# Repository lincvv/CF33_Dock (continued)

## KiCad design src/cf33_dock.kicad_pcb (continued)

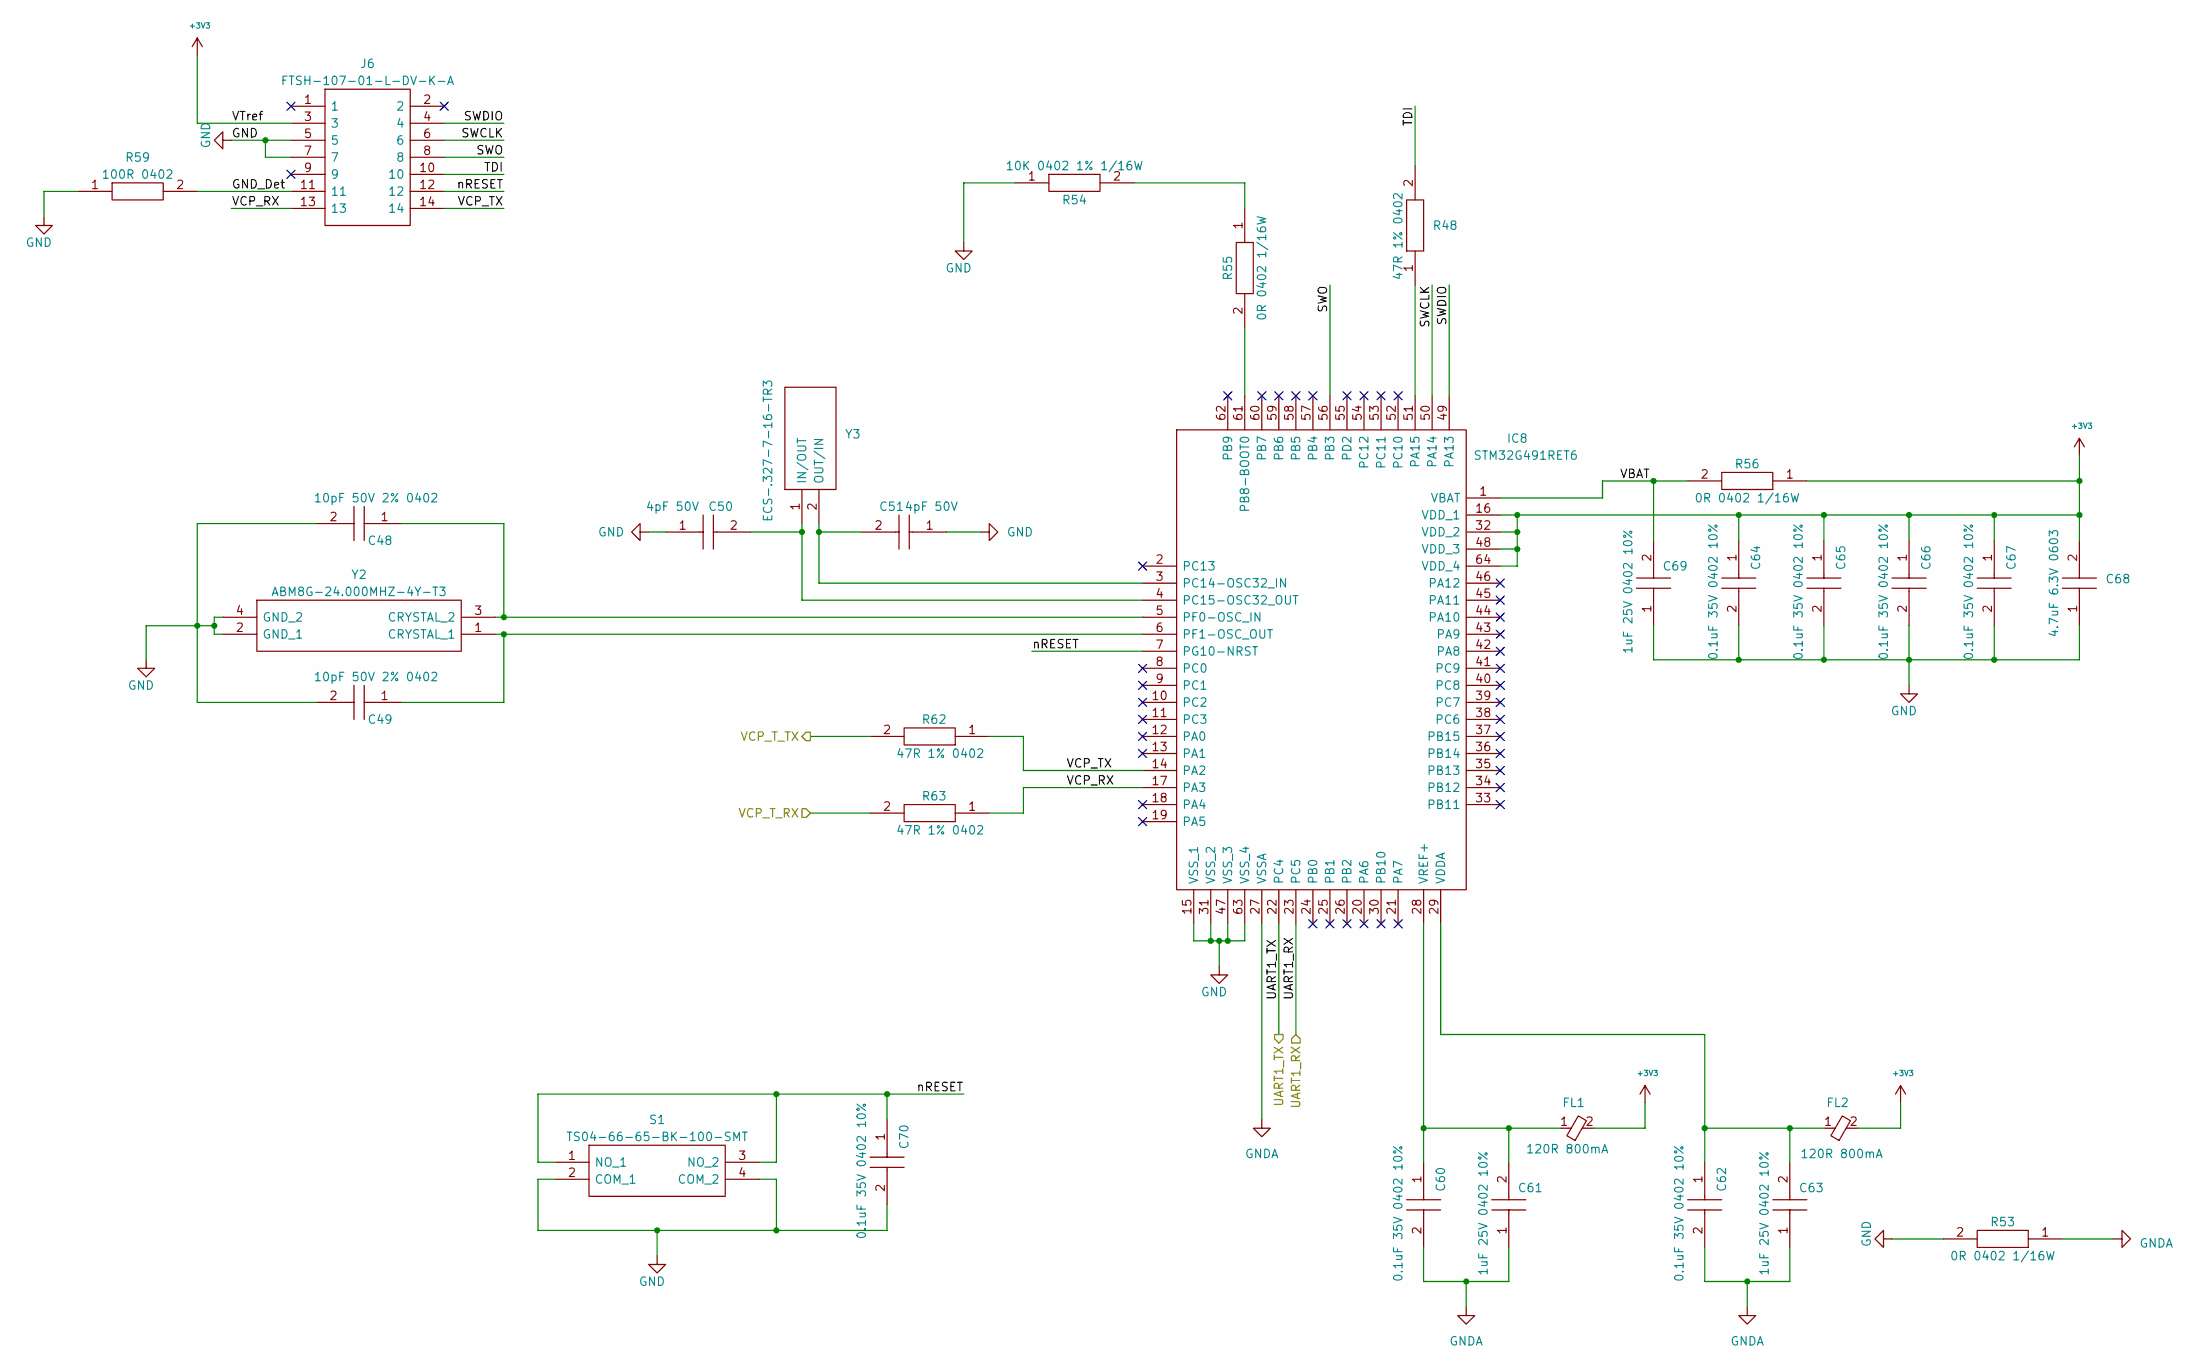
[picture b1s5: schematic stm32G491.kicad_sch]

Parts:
C48, C49: 10pF 50V 2% 0402; C_0402_1005Metric; Manufacturer_Part_Number GJM1555C1H100GB01D; Mouser Part Number 81-GJM1555C1H100GB01
C50, C51: 4pF 50V; R_0402_1005Metric; Manufacturer_Part_Number CQ0402CRNPO9BN4R0
C60, C62, C64, C65, C66, C67, C70: 0.1uF 35V 0402 10%; C_0402_1005Metric; Manufacturer_Part_Number CGA2B3X7R1V104K050BB; Mouser Part Number 810-CGA2B3X7R1V104K
C61, C63, C69: 1uF 25V 0402 10%; C_0402_1005Metric; Manufacturer_Part_Number GRM155R61E105KA12D; Mouser Part Number 81-GRM155R61E105KA2D
C68: 4.7uF 6.3V 0603; CAPC1608X90N; Manufacturer_Part_Number JMK107BB7475KA-T; Mouser Part Number 963-JMK107BB7475KA-T
FL1, FL2: 120R 800mA; BLM18AG102BH1D; Manufacturer_Part_Number BLM18AG121SN1D; Mouser Part Number 81-BLM11A121S
IC8: STM32G491RET6; QFP50P1200X1200X160-64N; Manufacturer_Part_Number STM32G491RET6; Mouser Part Number 511-STM32G491RET6
J6: FTSH-107-01-L-DV-K-A; FTSH-107-XX-YYY-DV-K-A; Manufacturer_Part_Number FTSH-107-01-L-DV-K-A; Mouser Part Number 200-FTSH10701LDVKA
R48, R62, R63: 47R 1% 0402; R_0402_1005Metric; Manufacturer_Part_Number CR0402-FX-47R0GLF
R53, R55, R56: 0R 0402 1/16W; R_0402_1005Metric; Manufacturer_Part_Number CRCW04020000ZSTD; Mouser Part Number 71-CRCW0402-0
R54: 10K 0402 1% 1/16W; R_0402_1005Metric; Manufacturer_Part_Number AC0402FR-0710KL; Mouser Part Number 603-AC0402FR-0710KL
R59: 100R 0402; R_0402_1005Metric; Manufacturer_Part_Number CRCW0402100RFKEDC; Mouser Part Number 71-CRCW0402100RFKEDC
S1: TS04-66-65-BK-100-SMT; TS046665BK100SMT; Manufacturer_Part_Number TS04-66-65-BK-100-SMT; Mouser Part Number 179-TS046665BK100SMT
Y2: ABM8G-24.000MHZ-4Y-T3; ABM8G24000MHZ4YT3; Mouser Part Number 815-ABM8G-24-4YT3
Y3: ECS-.327-7-16-TR3; ECS327716TR3; Manufacturer_Part_Number ECS-.327-7-16-TR3; Mouser Part Number 520-ECS-.327-7-16TR3

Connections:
+3V3: C64.1, C65.1, C66.1, C67.1, C68.2, FL1.2, FL2.2, IC8.16 (VDD_1), IC8.32 (VDD_2), IC8.48 (VDD_3), IC8.64 (VDD_4), J6.3, R56.1; also elsewhere on the board
/VCP_T_RX: R63.2; also elsewhere on the board
/VCP_T_TX: R62.2; also elsewhere on the board
/stm32G491/GND_Det: J6.11, R59.2
/stm32G491/SWCLK: IC8.50 (PA14), J6.6
/stm32G491/SWDIO: IC8.49 (PA13), J6.4
/stm32G491/SWO: IC8.56 (PB3), J6.8
/stm32G491/TDI: J6.10, R48.2
/stm32G491/UART1_RX: IC8.23 (PC5); also elsewhere on the board
/stm32G491/UART1_TX: IC8.22 (PC4); also elsewhere on the board
/stm32G491/VBAT: C69.2, IC8.1 (VBAT), R56.2
/stm32G491/VCP_RX: IC8.17 (PA3), J6.13, R63.1
/stm32G491/VCP_TX: IC8.14 (PA2), J6.14, R62.1
/stm32G491/nRESET: C70.1, IC8.7 (PG10-NRST), J6.12, S1.1 (NO_1), S1.3 (NO_2)
GND: C48.2, C49.2, C50.1, C51.1, C64.2, C65.2, C66.2, C67.2, C68.1, C69.1, C70.2, IC8.15 (VSS_1), IC8.31 (VSS_2), IC8.47 (VSS_3), IC8.63 (VSS_4), J6.5, J6.7, R53.2, R54.1, R59.1, S1.2 (COM_1), S1.4 (COM_2), Y2.2 (GND_1), Y2.4 (GND_2); also elsewhere on the board
GNDA: C60.2, C61.1, C62.2, C63.1, IC8.27 (VSSA), R53.1
unnamed: IC8.51 (PA15), R48.1
unnamed: IC8.61 (PB8-BOOT0), R55.2
unnamed: C51.2, IC8.3 (PC14-OSC32_IN), Y3.2 (OUT/IN)
unnamed: C50.2, IC8.4 (PC15-OSC32_OUT), Y3.1 (IN/OUT)
unnamed: C48.1, IC8.5 (PF0-OSC_IN), Y2.3 (CRYSTAL_2)
unnamed: C49.1, IC8.6 (PF1-OSC_OUT), Y2.1 (CRYSTAL_1)
unnamed: C62.1, C63.2, FL2.1, IC8.29 (VDDA)
unnamed: C60.1, C61.2, FL1.1, IC8.28 (VREF+)
unnamed: R54.2, R55.1

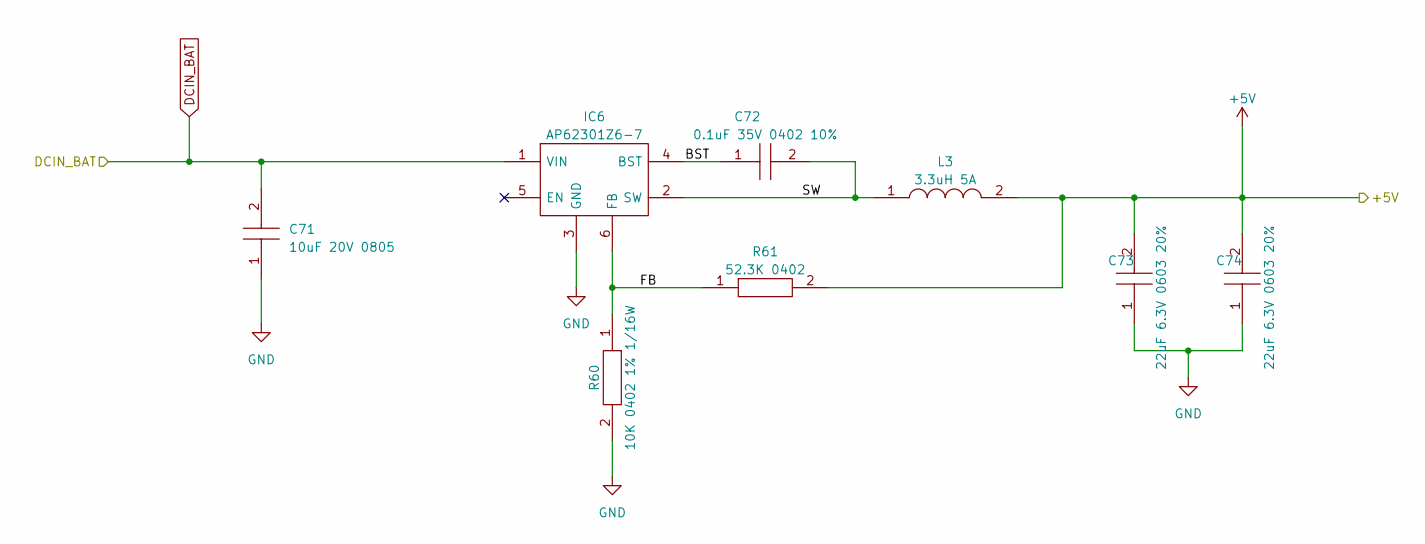
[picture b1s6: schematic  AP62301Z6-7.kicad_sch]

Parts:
C71: 10uF 20V 0805; C_0805_2012Metric; Manufacturer_Part_Number GRM21BR61D106KE15L; Mouser Part Number 81-GRM21BR61D106KE5L
C72: 0.1uF 35V 0402 10%; C_0402_1005Metric; Manufacturer_Part_Number CGA2B3X7R1V104K050BB; Mouser Part Number 810-CGA2B3X7R1V104K
C73, C74: 22uF 6.3V 0603 20%; C_0603_1608Metric; Manufacturer_Part_Number GRM188R60J226MEA0D; Mouser Part Number 81-GRM188R60J226ME0D
IC6: AP62301Z6-7; SOTFL50P162X60-6N; Manufacturer_Part_Number AP62301Z6-7; Mouser Part Number 621-AP62301Z6-7
L3: 3.3uH 5A; VLS6045; Manufacturer_Part_Number VLS6045AF-3R3N; Mouser Part Number 810-VLS6045AF-3R3N
R60: 10K 0402 1% 1/16W; R_0402_1005Metric; Manufacturer_Part_Number AC0402FR-0710KL; Mouser Part Number 603-AC0402FR-0710KL
R61: 52.3K 0402; R_0402_1005Metric; Manufacturer_Part_Number ERJ-2RKF5232X; Mouser Part Number 667-ERJ-2RKF5232X

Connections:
+5V: C73.2, C74.2, L3.2, R61.2; also elsewhere on the board
/DCIN_TO_5V/BST: C72.1, IC6.4 (BST)
/DCIN_TO_5V/FB: IC6.6 (FB), R60.1, R61.1
/DCIN_TO_5V/SW: C72.2, IC6.2 (SW), L3.1
DCIN_BAT: C71.2, IC6.1 (VIN); also elsewhere on the board
GND: C71.1, C73.1, C74.1, IC6.3 (GND), R60.2; also elsewhere on the board

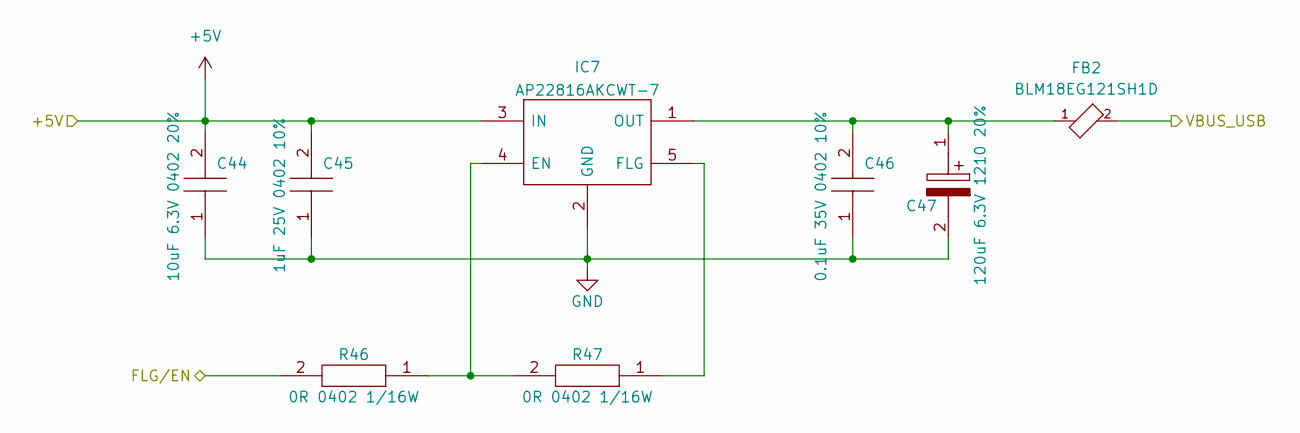
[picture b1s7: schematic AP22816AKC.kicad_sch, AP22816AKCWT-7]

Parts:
C44: 10uF 6.3V 0402 20%; C_0402_1005Metric; Manufacturer_Part_Number GRM155R60J106ME15D; Mouser Part Number 81-GRM155R60J106ME5D
C45: 1uF 25V 0402 10%; C_0402_1005Metric; Manufacturer_Part_Number GRM155R61E105KA12D; Mouser Part Number 81-GRM155R61E105KA2D
C46: 0.1uF 35V 0402 10%; C_0402_1005Metric; Manufacturer_Part_Number CGA2B3X7R1V104K050BB; Mouser Part Number 810-CGA2B3X7R1V104K
C47: 120uF 6.3V 1210 20%; C_1210_3225Metric; Manufacturer_Part_Number 6TPE120MAZB; Mouser Part Number 667-6TPE120MAZB
FB2: BLM18EG121SH1D; Manufacturer_Part_Number BLM18EG121SH1D; Mouser Part Number 81-BLM18EG121SH1D
IC7: AP22816AKCWT-7; SOT95P280X100-5N; Mouser Part Number 621-AP22816AKCWT-7
R46, R47: 0R 0402 1/16W; R_0402_1005Metric; Manufacturer_Part_Number CRCW04020000ZSTD; Mouser Part Number 71-CRCW0402-0

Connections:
+5V: C44.2, C45.2, IC7.3 (IN); also elsewhere on the board
/USB HUB/PRT_CTL4: R46.2; also elsewhere on the board
/usb_con/VBUS_USB2_P4: FB2.2; also elsewhere on the board
GND: C44.1, C45.1, C46.1, C47.2, IC7.2 (GND); also elsewhere on the board
unnamed: IC7.4 (EN), R46.1, R47.2
unnamed: IC7.5 (FLG), R47.1
unnamed: C46.2, C47.1, FB2.1, IC7.1 (OUT)

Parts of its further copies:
C22, C52, C56: 10uF 6.3V 0402 20%; C_0402_1005Metric; Manufacturer_Part_Number GRM155R60J106ME15D; Mouser Part Number 81-GRM155R60J106ME5D
C23, C53, C57: 1uF 25V 0402 10%; C_0402_1005Metric; Manufacturer_Part_Number GRM155R61E105KA12D; Mouser Part Number 81-GRM155R61E105KA2D
C24, C54, C58: 0.1uF 35V 0402 10%; C_0402_1005Metric; Manufacturer_Part_Number CGA2B3X7R1V104K050BB; Mouser Part Number 810-CGA2B3X7R1V104K
C25, C55, C59: 120uF 6.3V 1210 20%; C_1210_3225Metric; Manufacturer_Part_Number 6TPE120MAZB; Mouser Part Number 667-6TPE120MAZB
FB1, FB3, FB4: BLM18EG121SH1D; Manufacturer_Part_Number BLM18EG121SH1D; Mouser Part Number 81-BLM18EG121SH1D
IC3, IC9, IC10: AP22816AKCWT-7; SOT95P280X100-5N; Mouser Part Number 621-AP22816AKCWT-7
R35, R36, R49, R50, R51, R52: 0R 0402 1/16W; R_0402_1005Metric; Manufacturer_Part_Number CRCW04020000ZSTD; Mouser Part Number 71-CRCW0402-0

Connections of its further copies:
+5V: C22.2, C23.2, C52.2, C53.2, C56.2, C57.2, IC3.3 (IN), IC9.3 (IN), IC10.3 (IN); also elsewhere on the board
/USB HUB/PRT_CTL1: R49.2; also elsewhere on the board
/USB HUB/PRT_CTL2: R51.2; also elsewhere on the board
/USB HUB/PRT_CTL3: R35.2; also elsewhere on the board
/usb_con/VBUS_USB2_P1: FB3.2; also elsewhere on the board
/usb_con/VBUS_USB2_P2: FB4.2; also elsewhere on the board
/usb_con/VBUS_USB2_P3: FB1.2; also elsewhere on the board
GND: C22.1, C23.1, C24.1, C25.2, C52.1, C53.1, C54.1, C55.2, C56.1, C57.1, C58.1, C59.2, IC3.2 (GND), IC9.2 (GND), IC10.2 (GND); also elsewhere on the board
unnamed: IC3.4 (EN), R35.1, R36.2
unnamed: IC3.5 (FLG), R36.1
unnamed: C24.2, C25.1, FB1.1, IC3.1 (OUT)
unnamed: IC9.4 (EN), R49.1, R50.2
unnamed: IC9.5 (FLG), R50.1
unnamed: C54.2, C55.1, FB3.1, IC9.1 (OUT)
unnamed: IC10.4 (EN), R51.1, R52.2
unnamed: IC10.5 (FLG), R52.1
unnamed: C58.2, C59.1, FB4.1, IC10.1 (OUT)

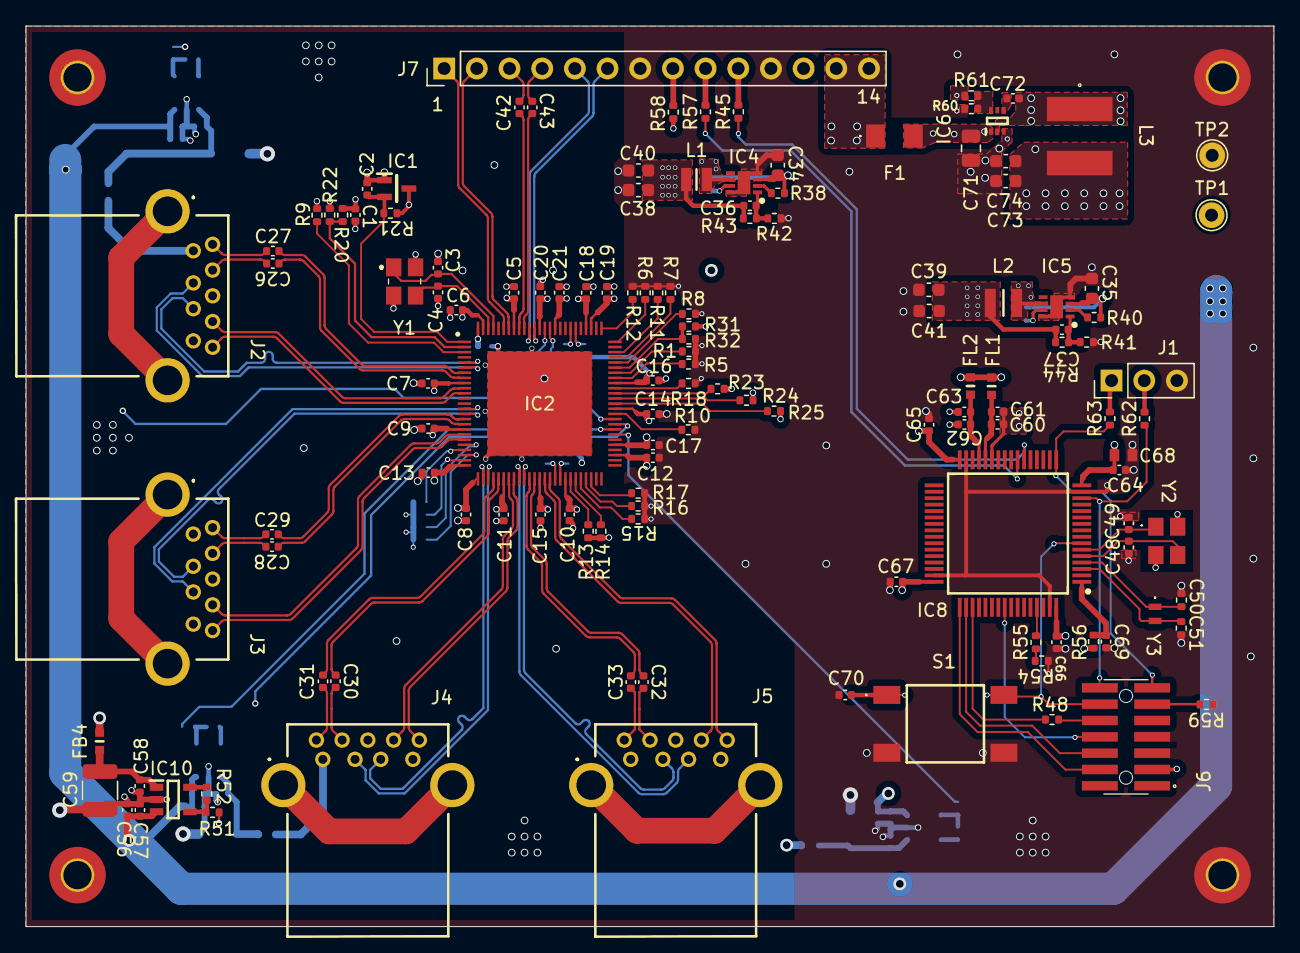
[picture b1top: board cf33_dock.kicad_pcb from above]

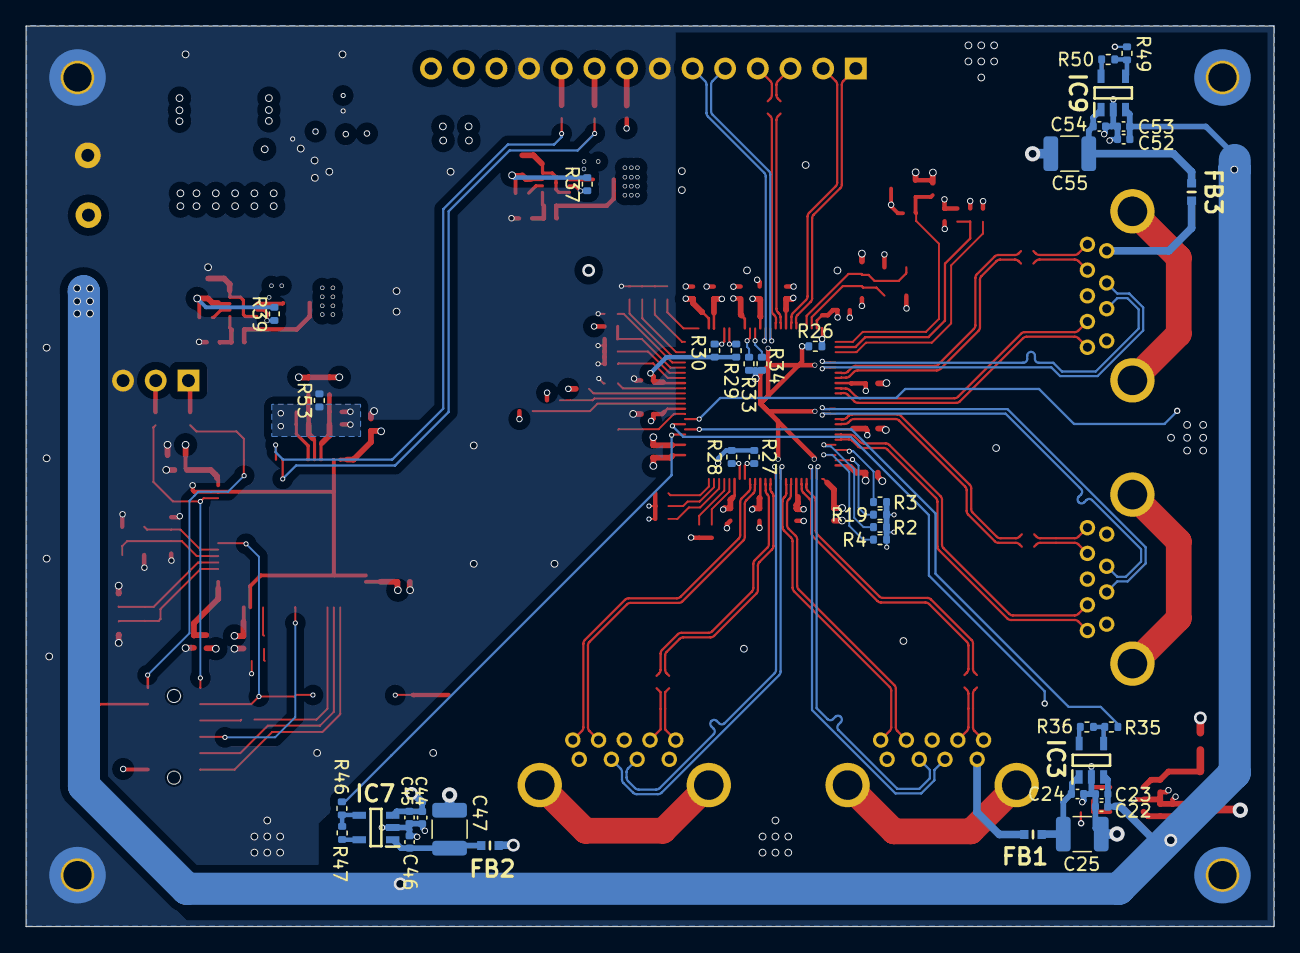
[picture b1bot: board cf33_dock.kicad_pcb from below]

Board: 4 copper layers, 97.0 x 70.0 mm, 170 parts (38 on the bottom side), 138 nets.

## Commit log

2023-07-29 add(img)
2023-07-29 clean
2023-07-29 fix(readme)
